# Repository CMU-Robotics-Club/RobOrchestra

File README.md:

RobOrchestra
=============

Welcome to RobOrchestra! RobOrchestra is an ongoing project in the Carnegie Mellon Robotics Club that aims to explore the creative possibilities for robotic instruments. We design, build and program robots that read music from MIDI data in order to put on musical performances. Our goal is to create a full robotic orchestra that is able to play from arrangements from standard MIDI files, and is also able to "improvise" unique polyphonic music in real time based off of music generation algorithms developed by our team.

Check out this demo video: https://drive.google.com/open?id=1UAF38HtQlL7tU6Xmdl4eHLXhHpyFQM5X

### How it works.
	
The robots, all powered by Arduinos with MIDI shields, operate via a distributed network. A laptop acts as the "conductor", transmitting MIDI siginals through the network of robots. Each robot reads the data and picks out its own part, and then plays it accordingly. We use Processing, a powerful music programming language, to control the orchestra, however it should work with nearly any MIDI software.

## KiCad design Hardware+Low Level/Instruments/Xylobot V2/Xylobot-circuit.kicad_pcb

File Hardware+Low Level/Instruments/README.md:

Instruments
===========

Each directory contains Arduino code, CAD files and documentation for each of our Robotic Instruments.

### Completed Robots
* tomBot
* snareBot
* xyloBot

### In Progress Robots
* ukuleleBot
* roboOboe
* harmonicaBot
* ViolinBot
* XyloBot V2

(Older, unused robot designs can be found in the "archives" directory.)

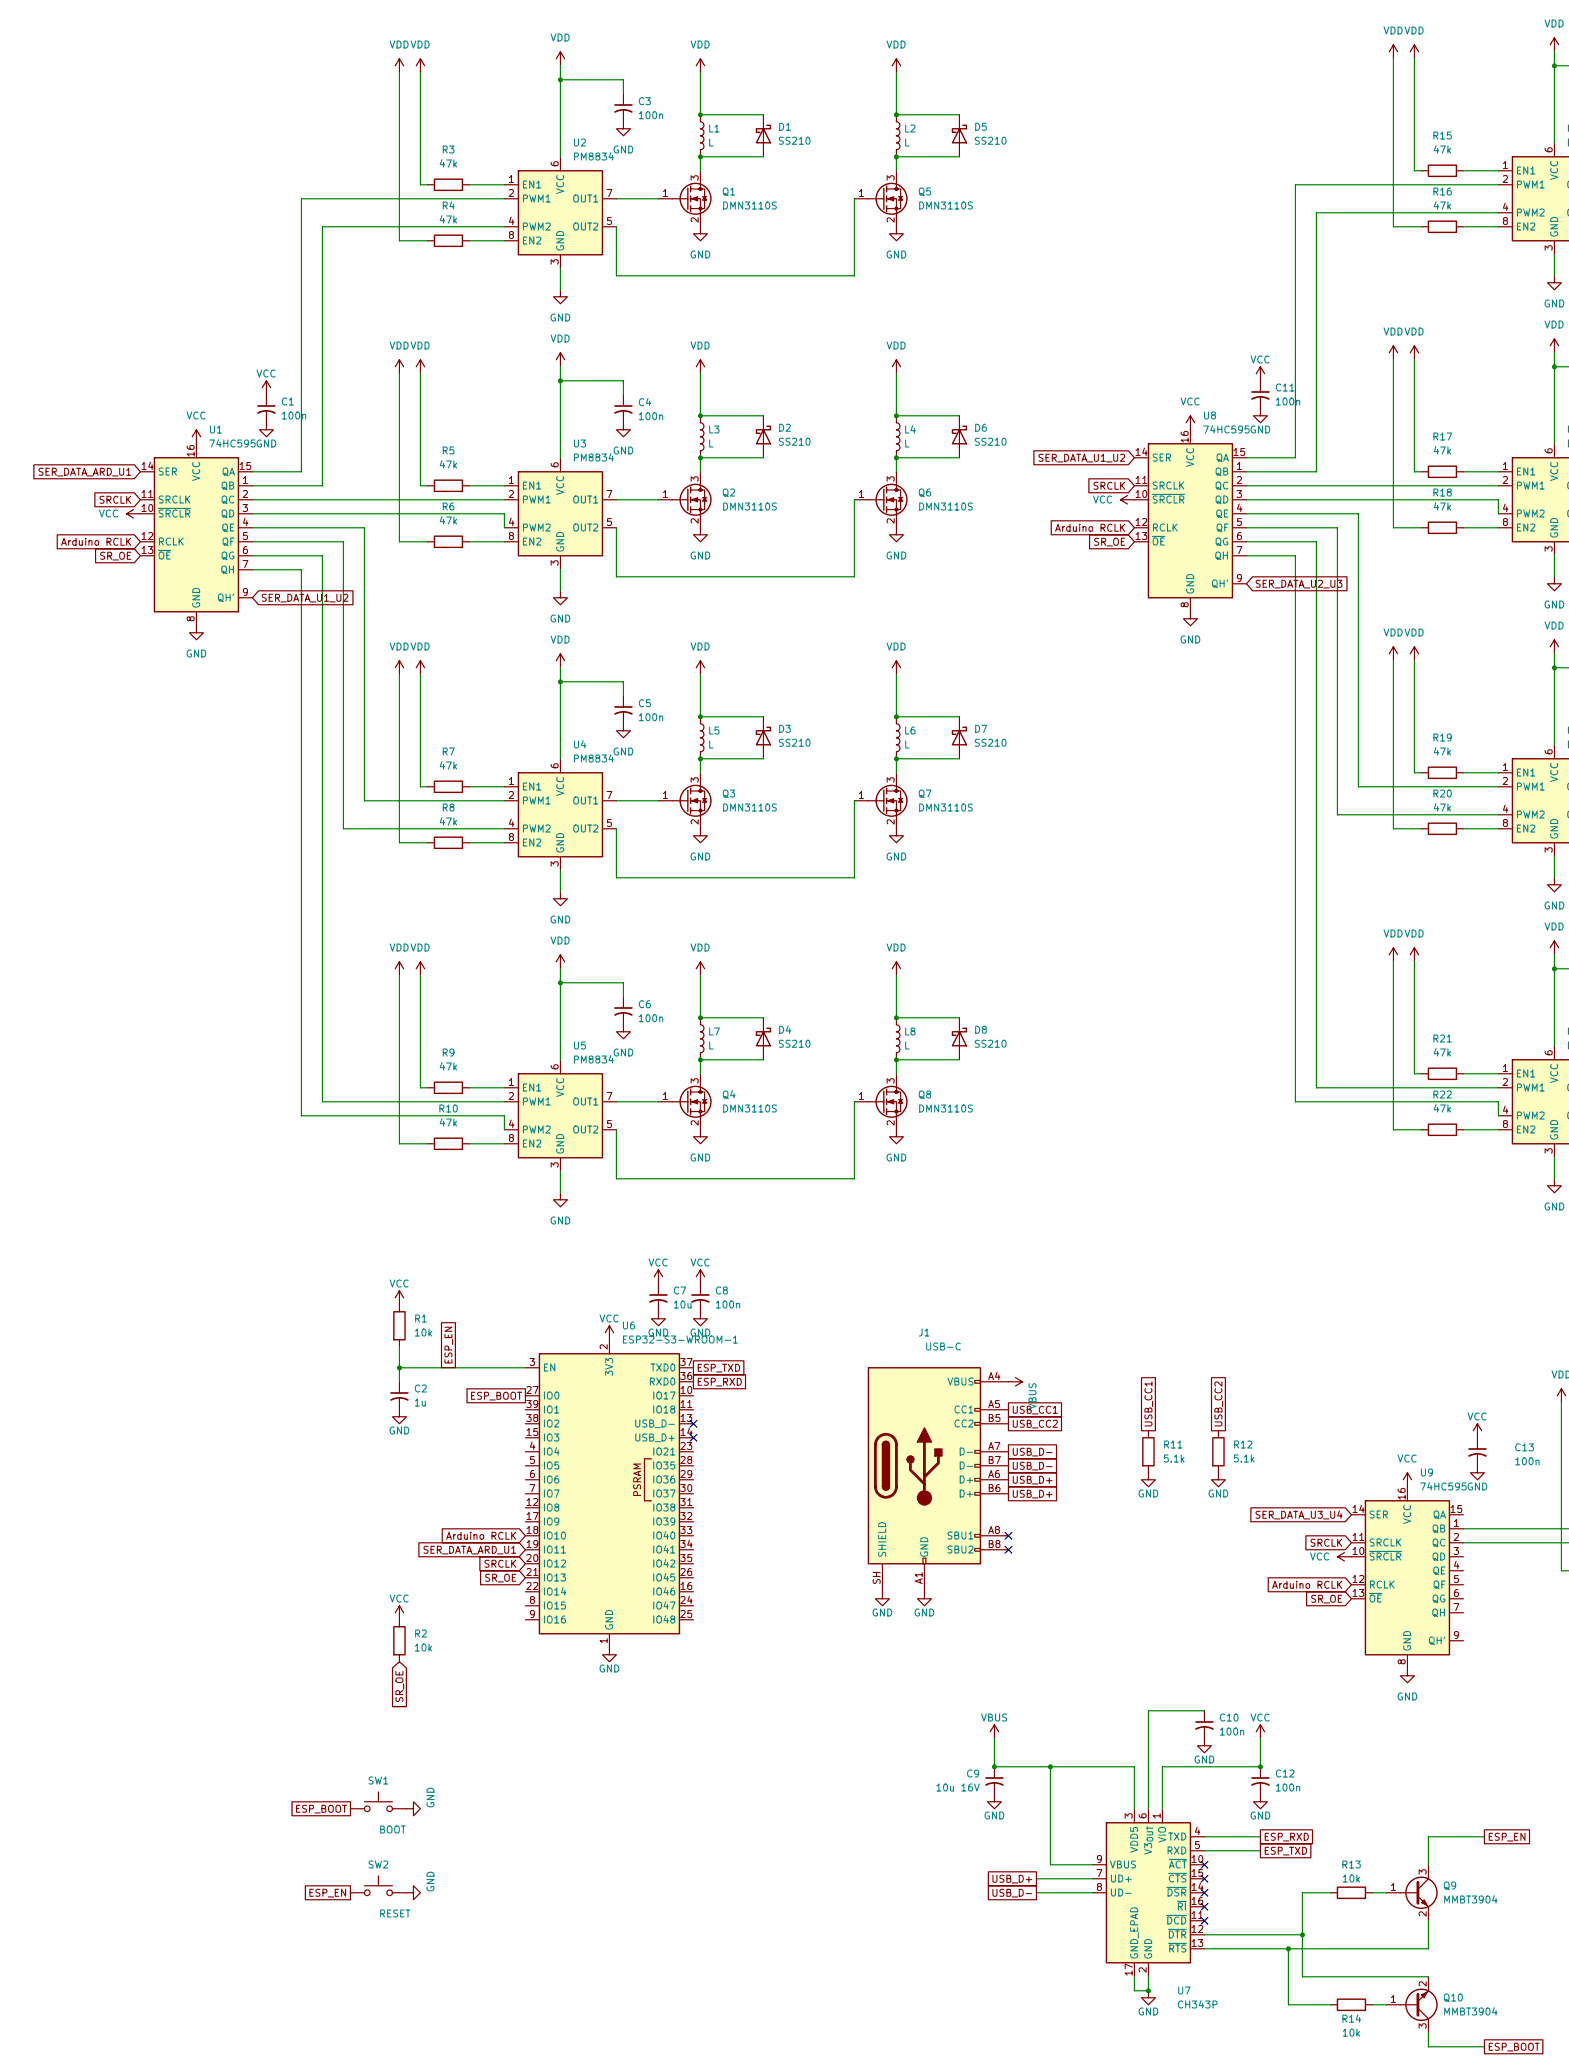
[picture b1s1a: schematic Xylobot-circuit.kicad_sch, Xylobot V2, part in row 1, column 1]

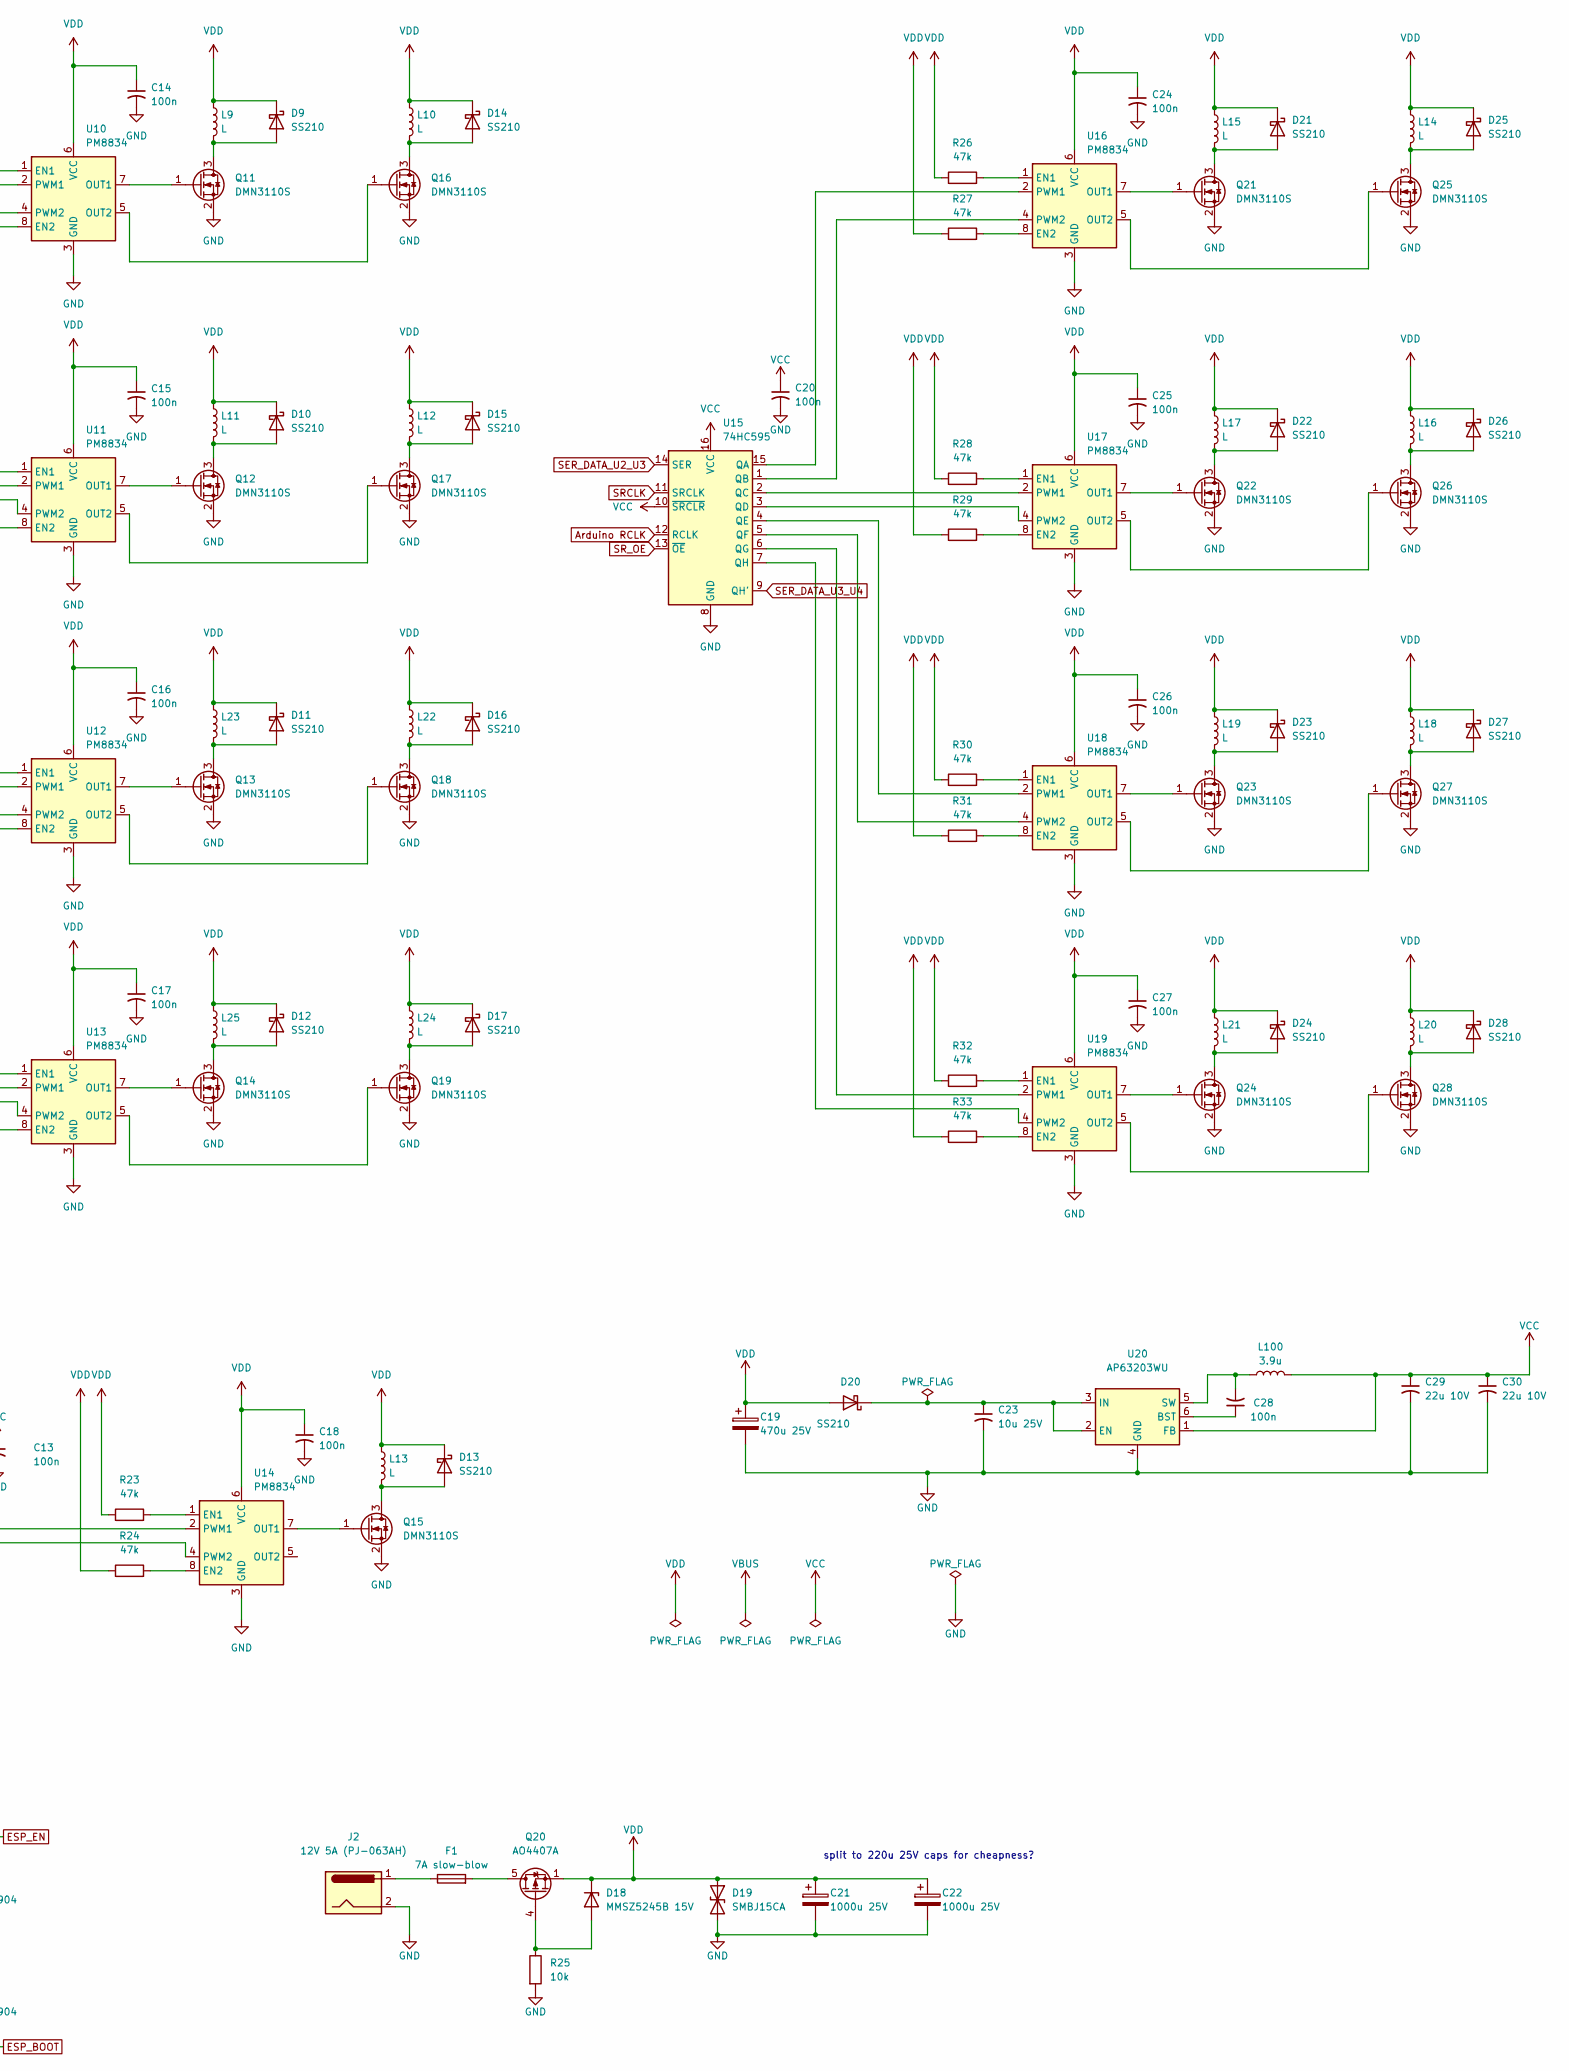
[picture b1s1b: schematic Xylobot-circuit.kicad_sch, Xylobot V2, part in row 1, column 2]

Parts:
C1, C3, C4, C5, C6, C8, C10, C11, C12, C13, C14, C15, C16, C17, C18, C20, C24, C25, C26, C27, C28: 100n; C_0603_1608Metric
C2: 1u; C_0603_1608Metric
C7: 10u; C_0805_2012Metric
C9: 10u 16V; C_0805_2012Metric
C19: 470u 25V; CP_Radial_D10.0mm_P5.00mm
C21, C22: 1000u 25V; CP_Radial_D10.0mm_P5.00mm
C23: 10u 25V; C_1206_3216Metric
C29, C30: 22u 10V; C_0805_2012Metric
D1, D2, D3, D4, D5, D6, D7, D8, D9, D10, D11, D12, D13, D14, D15, D16, D17, D20, D21, D22, D23, D24, D25, D26, D27, D28: SS210; D_SMA
D18: MMSZ5245B 15V; D_SOD-123
D19: SMBJ15CA; D_SMB
F1: 7A slow-blow; Fuse_1210_3225Metric
J1: USB-C; USB_C_Receptacle_HRO_TYPE-C-31-M-12
J2: 12V 5A (PJ-063AH); BarrelJack_CUI_PJ-063AH_Horizontal
L1, L2, L3, L4, L5, L6, L7, L8, L9, L10, L11, L12, L13, L14, L15, L16, L17, L18, L19, L20, L21, L22, L23, L24, L25: L; TerminalBlock_Phoenix_MKDS-1,5-2-5.08_1x02_P5.08mm_Horizont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
L100: 3.9u; L_Bourns-SRN4018
Q1, Q2, Q3, Q4, Q5, Q6, Q7, Q8, Q11, Q12, Q13, Q14, Q15, Q16, Q17, Q18, Q19, Q21, Q22, Q23, Q24, Q25, Q26, Q27, Q28: DMN3110S; SOT-23
Q9, Q10: MMBT3904; SOT-23
Q20: AO4407A; SOIC-8_3.9x4.9mm_P1.27mm
R1, R2, R13, R14, R25: 10k; R_0603_1608Metric
R3, R4, R5, R6, R7, R8, R9, R10, R15, R16, R17, R18, R19, R20, R21, R22, R23, R24, R26, R27, R28, R29, R30, R31, R32, R33: 47k; R_0603_1608Metric
R11, R12: 5.1k; R_0603_1608Metric
SW1: BOOT; SW_PUSH_6mm
SW2: RESET; SW_PUSH_6mm
U1, U8, U9, U15: 74HC595; SOIC-16_3.9x9.9mm_P1.27mm
U2, U3, U4, U5, U10, U11, U12, U13, U14, U16, U17, U18, U19: PM8834; SOIC-8_3.9x4.9mm_P1.27mm
U6: ESP32-S3-WROOM-1
U7: CH343P; WCH_QFN-16-1EP_3x3mm_P0.5mm_EP1.8x1.8mm
U20: AP63203WU; TSOT-23-6

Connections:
Arduino RCLK: U1.12 (RCLK), U6.18 (IO10), U8.12 (RCLK), U9.12 (RCLK), U15.12 (RCLK)
ESP_BOOT: Q10.3 (C), SW1.1, U6.27 (IO0)
ESP_EN: C2.1, Q9.3 (C), R1.2, SW2.1, U6.3 (EN)
ESP_RXD: U6.36 (RXD0), U7.4 (TXD)
ESP_TXD: U6.37 (TXD0), U7.5 (RXD)
GND: C1.2, C2.2, C3.2, C4.2, C5.2, C6.2, C7.2, C8.2, C9.2, C10.2, C11.2, C12.2, C13.2, C14.2, C15.2, C16.2, C17.2, C18.2, C19.2, C20.2, C21.2, C22.2, C23.2, C24.2, C25.2, C26.2, C27.2, C29.2, C30.2, D19.2 (A2), J1.A1 (GND), J1.A12 (GND), J1.B1 (GND), J1.B12 (GND), J1.SH (SHIELD), J2.2, Q1.2 (S), Q2.2 (S), Q3.2 (S), Q4.2 (S), Q5.2 (S), Q6.2 (S), Q7.2 (S), Q8.2 (S), Q11.2 (S), Q12.2 (S), Q13.2 (S), Q14.2 (S), Q15.2 (S), Q16.2 (S), Q17.2 (S), Q18.2 (S), Q19.2 (S), Q21.2 (S), Q22.2 (S), Q23.2 (S), Q24.2 (S), Q25.2 (S), Q26.2 (S), Q27.2 (S), Q28.2 (S), R11.2, R12.2, R25.2, SW1.2, SW2.2, U1.8 (GND), U2.3 (GND), U3.3 (GND), U4.3 (GND), U5.3 (GND), U6.1 (GND), U6.40 (GND), U6.41 (GND), U7.2 (GND), U7.17 (GND_EPAD), U8.8 (GND), U9.8 (GND), U10.3 (GND), U11.3 (GND), U12.3 (GND), U13.3 (GND), U14.3 (GND), U15.8 (GND), U16.3 (GND), U17.3 (GND), U18.3 (GND), U19.3 (GND), U20.4 (GND)
unnamed: D1.2 (A), L1.2, Q1.3 (D)
unnamed: D2.2 (A), L3.2, Q2.3 (D)
unnamed: D3.2 (A), L5.2, Q3.3 (D)
unnamed: D4.2 (A), L7.2, Q4.3 (D)
unnamed: D5.2 (A), L2.2, Q5.3 (D)
unnamed: D6.2 (A), L4.2, Q6.3 (D)
unnamed: D7.2 (A), L6.2, Q7.3 (D)
unnamed: D8.2 (A), L8.2, Q8.3 (D)
unnamed: D9.2 (A), L9.2, Q11.3 (D)
unnamed: D10.2 (A), L11.2, Q12.3 (D)
unnamed: D11.2 (A), L23.2, Q13.3 (D)
unnamed: D12.2 (A), L25.2, Q14.3 (D)
unnamed: D13.2 (A), L13.2, Q15.3 (D)
unnamed: D14.2 (A), L10.2, Q16.3 (D)
unnamed: D15.2 (A), L12.2, Q17.3 (D)
unnamed: D16.2 (A), L22.2, Q18.3 (D)
unnamed: D17.2 (A), L24.2, Q19.3 (D)
unnamed: D18.2 (A), Q20.4 (G), R25.1
unnamed: C23.1, D20.1 (K), U20.2 (EN), U20.3 (IN)
unnamed: D21.2 (A), L15.2, Q21.3 (D)
unnamed: D22.2 (A), L17.2, Q22.3 (D)
unnamed: D23.2 (A), L19.2, Q23.3 (D)
unnamed: D24.2 (A), L21.2, Q24.3 (D)
unnamed: D25.2 (A), L14.2, Q25.3 (D)
unnamed: D26.2 (A), L16.2, Q26.3 (D)
unnamed: D27.2 (A), L18.2, Q27.3 (D)
unnamed: D28.2 (A), L20.2, Q28.3 (D)
unnamed: F1.1, J2.1
unnamed: F1.2, Q20.5 (D), Q20.6 (D), Q20.7 (D), Q20.8 (D)
unnamed: Q1.1 (G), U2.7 (OUT1)
unnamed: Q2.1 (G), U3.7 (OUT1)
unnamed: Q3.1 (G), U4.7 (OUT1)
unnamed: Q4.1 (G), U5.7 (OUT1)
unnamed: Q5.1 (G), U2.5 (OUT2)
unnamed: Q6.1 (G), U3.5 (OUT2)
unnamed: Q7.1 (G), U4.5 (OUT2)
unnamed: Q8.1 (G), U5.5 (OUT2)
unnamed: Q9.1 (B), R13.2
unnamed: Q9.2 (E), R14.1, U7.13 (~RTS)
unnamed: Q10.1 (B), R14.2
unnamed: Q10.2 (E), R13.1, U7.12 (~DTR)
unnamed: Q11.1 (G), U10.7 (OUT1)
unnamed: Q12.1 (G), U11.7 (OUT1)
unnamed: Q13.1 (G), U12.7 (OUT1)
unnamed: Q14.1 (G), U13.7 (OUT1)
unnamed: Q15.1 (G), U14.7 (OUT1)
unnamed: Q16.1 (G), U10.5 (OUT2)
unnamed: Q17.1 (G), U11.5 (OUT2)
unnamed: Q18.1 (G), U12.5 (OUT2)
unnamed: Q19.1 (G), U13.5 (OUT2)
unnamed: Q21.1 (G), U16.7 (OUT1)
unnamed: Q22.1 (G), U17.7 (OUT1)
unnamed: Q23.1 (G), U18.7 (OUT1)
unnamed: Q24.1 (G), U19.7 (OUT1)
unnamed: Q25.1 (G), U16.5 (OUT2)
unnamed: Q26.1 (G), U17.5 (OUT2)
unnamed: Q27.1 (G), U18.5 (OUT2)
unnamed: Q28.1 (G), U19.5 (OUT2)
unnamed: U1.15 (QA), U2.2 (PWM1)
unnamed: U1.1 (QB), U2.4 (PWM2)
unnamed: U1.2 (QC), U3.2 (PWM1)
unnamed: U1.3 (QD), U3.4 (PWM2)
unnamed: U1.4 (QE), U4.2 (PWM1)
unnamed: U1.5 (QF), U4.4 (PWM2)
unnamed: U1.6 (QG), U5.2 (PWM1)
unnamed: U1.7 (QH), U5.4 (PWM2)
unnamed: R3.2, U2.1 (EN1)
unnamed: R4.2, U2.8 (EN2)
unnamed: R5.2, U3.1 (EN1)
unnamed: R6.2, U3.8 (EN2)
unnamed: R7.2, U4.1 (EN1)
unnamed: R8.2, U4.8 (EN2)
unnamed: R9.2, U5.1 (EN1)
unnamed: R10.2, U5.8 (EN2)
unnamed: C10.1, U7.6 (V3_{OUT})
unnamed: R15.2, U10.1 (EN1)
unnamed: R16.2, U10.8 (EN2)
unnamed: U8.15 (QA), U10.2 (PWM1)
unnamed: U8.1 (QB), U10.4 (PWM2)
unnamed: R17.2, U11.1 (EN1)
unnamed: R18.2, U11.8 (EN2)
unnamed: U8.2 (QC), U11.2 (PWM1)
unnamed: U8.3 (QD), U11.4 (PWM2)
unnamed: R19.2, U12.1 (EN1)
unnamed: R20.2, U12.8 (EN2)
unnamed: U8.4 (QE), U12.2 (PWM1)
unnamed: U8.5 (QF), U12.4 (PWM2)
unnamed: R21.2, U13.1 (EN1)
unnamed: R22.2, U13.8 (EN2)
unnamed: U8.6 (QG), U13.2 (PWM1)
unnamed: U8.7 (QH), U13.4 (PWM2)
unnamed: R23.2, U14.1 (EN1)
unnamed: R24.2, U14.8 (EN2)
unnamed: U9.1 (QB), U14.2 (PWM1)
unnamed: U9.2 (QC), U14.4 (PWM2)
unnamed: U15.15 (QA), U16.2 (PWM1)
unnamed: U15.1 (QB), U16.4 (PWM2)
unnamed: U15.2 (QC), U17.2 (PWM1)
unnamed: U15.3 (QD), U17.4 (PWM2)
unnamed: U15.4 (QE), U18.2 (PWM1)
unnamed: U15.5 (QF), U18.4 (PWM2)
unnamed: U15.6 (QG), U19.2 (PWM1)
unnamed: U15.7 (QH), U19.4 (PWM2)
unnamed: R26.2, U16.1 (EN1)
unnamed: R27.2, U16.8 (EN2)
unnamed: R28.2, U17.1 (EN1)
unnamed: R29.2, U17.8 (EN2)
unnamed: R30.2, U18.1 (EN1)
unnamed: R31.2, U18.8 (EN2)
unnamed: R32.2, U19.1 (EN1)
unnamed: R33.2, U19.8 (EN2)
unnamed: C28.1, U20.6 (BST)
unnamed: C28.2, L100.1, U20.5 (SW)
SER_DATA_ARD_U1: U1.14 (SER), U6.19 (IO11)
SER_DATA_U1_U2: U1.9 (QH'), U8.14 (SER)
SER_DATA_U2_U3: U8.9 (QH'), U15.14 (SER)
SER_DATA_U3_U4: U9.14 (SER), U15.9 (QH')
SRCLK: U1.11 (SRCLK), U6.20 (IO12), U8.11 (SRCLK), U9.11 (SRCLK), U15.11 (SRCLK)
SR_OE: R2.2, U1.13 (~OE), U6.21 (IO13), U8.13 (~OE), U9.13 (~OE), U15.13 (~OE)
USB_CC1: J1.A5 (CC1), R11.1
USB_CC2: J1.B5 (CC2), R12.1
USB_D+: J1.A6 (D+), J1.B6 (D+), U7.7 (UD+)
USB_D-: J1.A7 (D-), J1.B7 (D-), U7.8 (UD-)
VBUS: C9.1, J1.A4 (VBUS), J1.A9 (VBUS), J1.B4 (VBUS), J1.B9 (VBUS), U7.3 (VDD5), U7.9 (VBUS)
VCC: C1.1, C7.1, C8.1, C11.1, C12.1, C13.1, C20.1, C29.1, C30.1, L100.2, R1.1, R2.1, U1.10 (~SRCLR), U1.16 (VCC), U6.2 (3V3), U7.1 (VIO), U8.10 (~SRCLR), U8.16 (VCC), U9.10 (~SRCLR), U9.16 (VCC), U15.10 (~SRCLR), U15.16 (VCC), U20.1 (FB)
VDD: C3.1, C4.1, C5.1, C6.1, C14.1, C15.1, C16.1, C17.1, C18.1, C19.1, C21.1, C22.1, C24.1, C25.1, C26.1, C27.1, D1.1 (K), D2.1 (K), D3.1 (K), D4.1 (K), D5.1 (K), D6.1 (K), D7.1 (K), D8.1 (K), D9.1 (K), D10.1 (K), D11.1 (K), D12.1 (K), D13.1 (K), D14.1 (K), D15.1 (K), D16.1 (K), D17.1 (K), D18.1 (K), D19.1 (A1), D20.2 (A), D21.1 (K), D22.1 (K), D23.1 (K), D24.1 (K), D25.1 (K), D26.1 (K), D27.1 (K), D28.1 (K), L1.1, L2.1, L3.1, L4.1, L5.1, L6.1, L7.1, L8.1, L9.1, L10.1, L11.1, L12.1, L13.1, L14.1, L15.1, L16.1, L17.1, L18.1, L19.1, L20.1, L21.1, L22.1, L23.1, L24.1, L25.1, Q20.1 (S), Q20.2 (S), Q20.3 (S), R3.1, R4.1, R5.1, R6.1, R7.1, R8.1, R9.1, R10.1, R15.1, R16.1, R17.1, R18.1, R19.1, R20.1, R21.1, R22.1, R23.1, R24.1, R26.1, R27.1, R28.1, R29.1, R30.1, R31.1, R32.1, R33.1, U2.6 (VCC), U3.6 (VCC), U4.6 (VCC), U5.6 (VCC), U10.6 (VCC), U11.6 (VCC), U12.6 (VCC), U13.6 (VCC), U14.6 (VCC), U16.6 (VCC), U17.6 (VCC), U18.6 (VCC), U19.6 (VCC)

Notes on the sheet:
split to 220u 25V caps for cheapness?

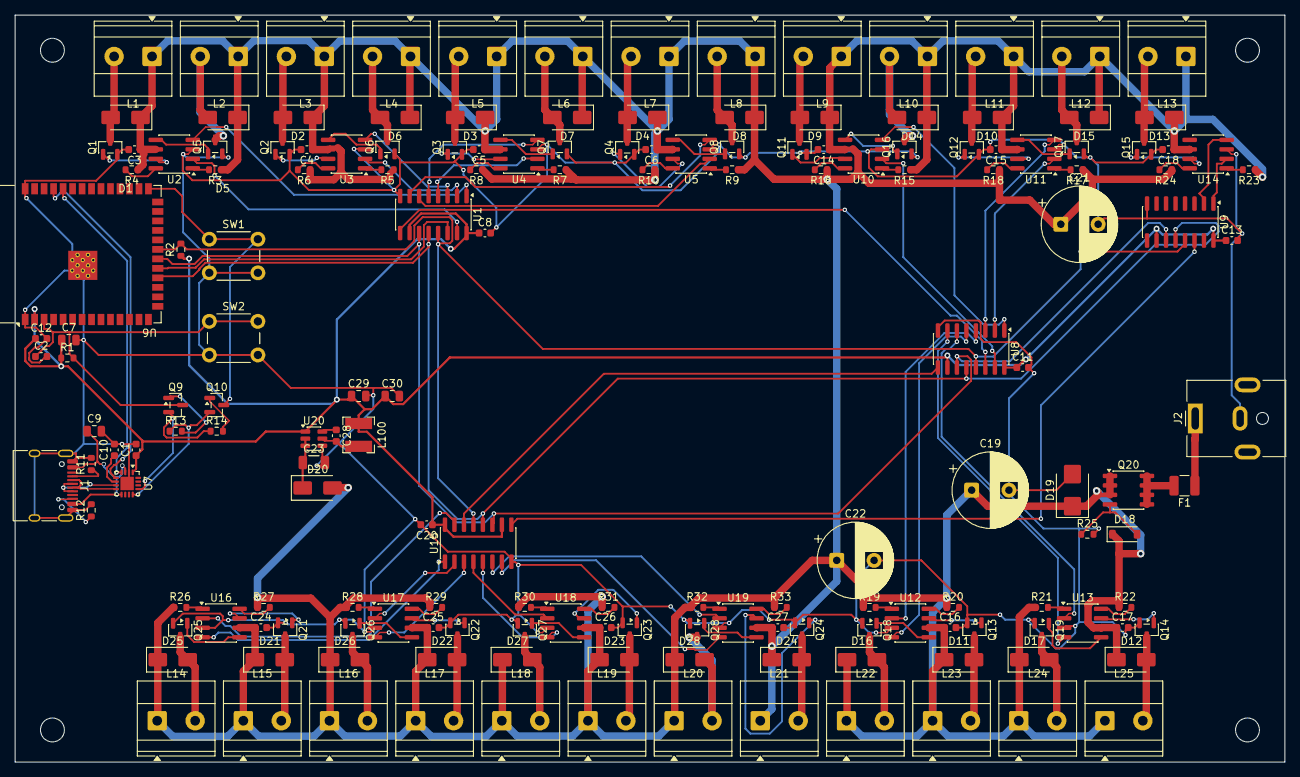
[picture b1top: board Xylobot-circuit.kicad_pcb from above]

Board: 2 copper layers, 170.0 x 100.0 mm, 174 parts (0 on the bottom side), 132 nets.

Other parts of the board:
H1, H2, H3, H4: MountingHole_3.2mm_M3

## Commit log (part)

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2017-11-13 Rhythm Updates
2017-11-13 BASIC MARKOV DOESNT COMPILE - TEMPORARY MAJOR CHANGES
    Changes are modifying all of basic markov, chorddetection, and playnotethread to take int arrays
2017-11-27 Removed unnecessary files in BasicMarkov
2017-11-27 Partially implemented proper chord playing in PlayNoteThread
2017-11-27 Fixed some flaws in chord detection with making assumptions based on order of notes inputted
2017-11-28 Made Chord Detection slightly more accurate when returning basic major and minor chords
2017-12-04 Played with chord detection. Changed PlayNoteThread to only play chords with probability 0.4. (Instead of a monkey banging on a keyboard, we have an unpredictable random monkey banging on a keyboard.)
2018-01-22 Updated tempo scale in interactive demo
2018-01-22 Actually committing the dominant 7th fix...
2018-01-29 Cleaned up xylobot low level. To do: Discretize time and teach the low-level code to go back in time on receiving MIDI messages.
2018-02-19 Updated xylobot code, moved BasicMarkov from Test Code to Music Generation Algorithms, renamed it ChordMarkov.
2018-02-19 Old Xylobot code retrieved, new Xylobot code cleaned up
2018-02-26 Updated Xylobot code (channel is 1, C# is remapped)
2018-03-05 Changing percussion channels in processing code
2018-03-19 Added musescore files for new tested songs
2018-03-19 Got the Ukelele Arduino code to compile (I hope it's the right file, and I'm pretty sure it compiles now and didn't before), but I'm not great with C, so I'm not sure it works at all. A good chunk of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
2018-03-26 Updated snarebot code
2018-03-26 CounterPointFirstSpecies and Generate added to CounterPointFirstSpecies Folder
2018-03-26 Fixed tom code. Turned off test messages on snare and tom code
2018-03-26 Fixed RULEFILTER to be basic implementation of creating random bass line
    It literally just removes the fifth. I will modify it to take in rules based on previously written notes later.
2018-04-02 Renamed DavidMarkov
2018-04-09 Added a test file for playing with SoundCipher things. It plays and writes a MIDI file of a chromatic scale to the data folder in the ScoreTest folder, which is in the TestCode folder.
2018-04-09 More playign with the score stuff. More comments.
2018-04-09 Added score to Generate
2018-04-09 got score to not play everything at once
2018-04-16 Changed solenoid pin numbers. Code not compiling; something about arrays not being correct...
2018-04-16 Updated ukulelebot code
2018-04-16 Compiles now
2018-04-16 Ukelelebot code works
2018-04-16 fixed everything
2018-04-18 Updated interactive demo
2018-04-23 Added Second Species pt. 2
2018-08-27 counterpoint changes and interactive demo changes
2018-10-29 Added CV_Interaction folder, which is where all open_cv final work should go
2018-11-01 Removed pesky .DS_Stores
2018-11-12 Point Vector Calculations
    (point vectors calculated, prints out point vector as well)
2018-11-12 Calculating velocity
2018-11-26 Added in blur, set fps of capture
2018-11-26 Update CV_Interaction.pde
    comment on line 117 about averaging the tempo to compensate for human error
2019-01-25 no message
2019-01-28 .DS_STORE be gone!
2019-02-06 Uses brightness/light detection to change volume
2019-02-18 Minor Jeopardy changes; copied Interactive Demo in case we add conducting
2019-02-19 Messed around with Markov_with_CV; still not picking up the object correctly.
2019-02-26 Seems to work a lot better now. The big change was detecting high, not low velocity, since that seems to be where I (as a human) put the beat, plus lets us be a bit more conservative with our beat bu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
    Also cleared some unnecessary print statements, since those were annoying
2019-03-01 Added starter code for Drumroller (WIP name). Potential Python solution to openCV problems.
    Requires openCV library to run. Use homebrew to get it.
2019-03-18 Fixed a typo. How do I run the code?
2019-04-02 added to drumroller.py
2019-04-16 got Drumroller to work without sending a message
2019-04-29 Added some test code and songs for single-note instruments (mostly for testing Robo-Oboe, but someone might find it useful later). We really should reorganize these folders, though; somehow the relev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
2019-05-20 Added RoboOboe TODOs
2019-09-28 added a file
2019-09-30 initial upload
2019-09-30 Add files via upload
    General Assembly for the robot
2019-10-07 Update general Assembly with Baseboard
2019-10-10 putting in parts
2019-10-14 inner servo housing part CAD file
2019-10-14 Add outer finger files via upload
2019-10-14 added servo housings to general assembly
2019-10-14 Files Elinora worked on 10-14
2019-10-16 Vector
    Sends data struct pointer with x,y,dx,dy inside it.
    Units are in pixels per millisecond.
    Put it in the right place this time lol
2019-10-16 Added file reading code but checking validity of string doesn't work yet
2019-10-16 Fixed bug where snare/tom msgs here being played by xylobot (causing c# note on). Now xylobot only accepts channel1 messages
2019-10-21 putting components into main assembly
2019-10-21 Putting everything into assembly
2019-10-21 steven's components
2019-10-21 inner servo housing STL file
2019-10-21 assembly update
2019-10-23 fixed matlab
2019-11-04 more CAD development
2019-11-06 Added I'm Yours MuseScore files
    And added Sharon's MATLAB test
2019-11-11 small update
2019-11-11 Pick Holder CAD
2019-11-13 Added The Scientist
2019-11-13 shape of you
2019-11-13 added payphone
2019-11-15 servo holder adjustment
2019-11-20 Read more data from pixy
2019-12-02 linear actuator code
2020-02-05 Added demo video
2020-02-21 Add files via upload
    Added comments for frequently-changed variables. The ultimate goal is to be able to run this from the command line, with those variables as inputs.
2020-03-18 Started work on a (buggy) Markov chain for chords
    Sorry if I'm stepping on someone's toes here, but I was travelling and bored.
    I've started implmenting the chord-based Markov chain in chordHMM. It's not a full HMM yet, as it doesn't do anything with the melody line. It also seems to have issues identifying chords. I'll see i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
2020-03-19 Fixed Edge Cases
    First chord in certain files (like "I'm Yours") is shorter by about 100 ticks than later chords, but that's the only weirdness I'm seeing now.
    If I'm bored with a large chunk of time, I'll start working on that melody reader, but I don't know if/when I'll get to that. If anyone wants to take over from here, feel free (but let me know so I d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
2020-11-01 Renamed folder
    Trying to fix errors for people cloning
2020-11-08 Added MultiSongChordMarkov
    Takes two songs, randomly transitions within/between them.
    Next steps:
    Use multiple songs?
    If an attempted transition fails, keep trying on all future notes until it works?
    (NOTE: Changed the State class so length==delay to make this work on Sam's demo songs, might need to look into this)
2020-11-15 Can (probably?) now play chords
    ...except our songs right now don't have chords. When I attempt to extract chords from the melody line, I correctly find the one melody note that's currently playing.
2020-11-22 Added Wagon Wheel score
2020-11-22 Modified multisong input to take in any number of inputs
    Bug - song index isn't incrementing properly
2020-12-06 Corrected MIDI files for Don't Stop Believing and With or Without You
2021-03-28 test noteToPos
2021-04-04 merged test code with wiring for ukueleCtrl
2021-04-11 A string moves in increments
2021-04-26 have notes play on various positions on string
2021-10-01 added handbell CAD files
2021-10-08 add PD control to ukuleleCtrl
2021-10-15 Comments for theremin integration
2021-10-29 Created ML music generation folder and jupyter notebook
2021-10-29 Beat detection?
    Not great. Triggers when we enter/leave field of view. TODO: Need to try testing with a non-deformable object while not wearing a blue shirt, preferably with someone who knows how to run the visualiz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
2021-11-12 Beat Detector Mostly Working
    Next steps: Track time between beats, send tempo to demo code
2021-11-19 Processing code for playing pitches and conducting scales
2021-11-19 Processing code to hopefully read pitch and volume
2021-11-19 Updated conducting test to follow red instead of blue
    The lights are blue-tinted in Roboclub, according to the Pixy - red performs much better
2023-01-05 Added PlaySong to play a MIDI file
    PlaySong plays all tracks of a MIDI file; Markov code with really long state length only plays one track plus maybe chords.
    It's still a bit hacky (I start up a bunch of threads and hope they don't interfere with each other or get out of sync), and ideally we'd find something that lets us play stuff through MuseScore dire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
2023-01-27 Jump-to-note probabilities in Interactive Demo fixed
    Also using InteractiveDemoNoConducting and deleting InteractiveDemo, as we never got around to making conducting work well enough to integrate yet
2023-02-17 Code cleanup
2023-04-10 Violinbot Code
    Not working yet, unclear if it's a code issue or a wiring issue
2023-10-13 Bugfix playMIDIconduct
2023-11-03 Readded threshold to Arduino conducting code
    Apparently the trick is to use a small float value; 1 is way too big
2024-01-26 pygame Test
    Sample code for pygame
2024-02-16 Transformer can save/load and play
    But not sure it's playing anything sensible
2024-02-16 ntoken size decrease
2024-02-23 PlaySong fixed, conducting renamed
2024-03-01 playSong2
2024-03-15 transformerPlay accepts midi file name
2024-03-22 Transformer somewhat working
    AuldLangSyne gets confused by repeated notes, otherwise seems okay.
    .model files are large and train fairly fast, so I'm going to stop committing those
2024-04-11 MIDIfromPitch
2024-04-12 ampScale fix
2024-04-17 Cleanup after Friday's demo
2024-04-25 Localization: Visuals, cont time. Working on 2D
2024-05-03 song position
2024-05-03 notes padding
2024-05-03 clean up noteArray
2024-08-26 Interactive Demo Fixed?
    surface.setSize() doesn't change Processing responsive area anymore? Super weird bug
2024-09-03 Reimplemented FFT localizer with matrix library
    Mostly not vectorized yet, so probably not much faster than what we had, but seems to be working?
    Seems to be jumping octaves in playback, though - I'll have to check on that at some point...
2024-09-17 Speed up fftLocalizer2DMatrix
    Just removing repeated calculations in for loops for now. TODO actually vectorize this thing
2024-10-08 Update fftLocalizer2DMatrixFast.pde
    Standard deviations now scale (hopefully correctly!) with number of buckets
2024-10-08 songPosition -> NoteArray class
2024-10-22 Git's being sad, committing this just in case
    And also to see what'll happen, hopefully I don't break anything
2024-10-22 NoteArray fixes
2024-10-22 buggy
2024-10-22 Cleanup and have resample not insert 0s
2024-10-29 test playRhythm
2024-11-05 MIDI file transform
2024-11-05 midiCompress + noteArray pattern fix
2024-11-12 Reduce empty measures at start of WWRY
2024-11-12 More cleanup
2024-11-26 Add Volume Tuning Program
2024-12-03 Non-repeating rhythm line
2025-02-06 fft non-repeated with filter
2025-02-06 filter working
2025-02-27 frequency detect fixes
2025-02-28 multiple pitch detect
2025-04-10 Fix end-of-measure?
2025-04-10 Add same-length track fix to the versions we'll be using
2025-04-10 archive intermediate versions of fft
2025-04-10 Hopefully use conducting data
    Should grab conducting data from computer camera, compare to beat counts from to-be-updated NoteArray, and use that for localization
2025-04-10 fft with note detection & conducting
2025-04-11 HOPEFULLY NOT BROKEN?
    Blind-copying tempoGaussMat update to all current code files. If something ends up broken in the near future, it's probably related to this
2025-04-17 Boolean toggles for notes/conducting
    Also some general parameter cleanup
2025-04-17 Read double-pattern 6/8 correctly
2025-04-17 call & response tests
2025-04-25 Needs more testing
    Normalized beatProbsArr correctly I hope. TODO test with oboe or something. Seems to mostly stick to whatever transposition it starts with, but it's hard to tell if it's correct without known notes. 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
2025-05-01 pitchdetect changes
2025-05-01 Update fftLocalizerTransposeDavidTest.pde
    Twinkle twinkle settings for oboe in quiet room, apparently
2025-09-14 Rename
2026-03-08 Add second MidiBus to interactive demos
    Idea is to have one MidiBus point to Xylobot and the other point to the Bluetooth stuff for the drums
2026-03-09 Quick DrumBot Commit
2026-03-12 changed drumbot md
2026-03-14 bettered latency and fixed mirrored weirdness
